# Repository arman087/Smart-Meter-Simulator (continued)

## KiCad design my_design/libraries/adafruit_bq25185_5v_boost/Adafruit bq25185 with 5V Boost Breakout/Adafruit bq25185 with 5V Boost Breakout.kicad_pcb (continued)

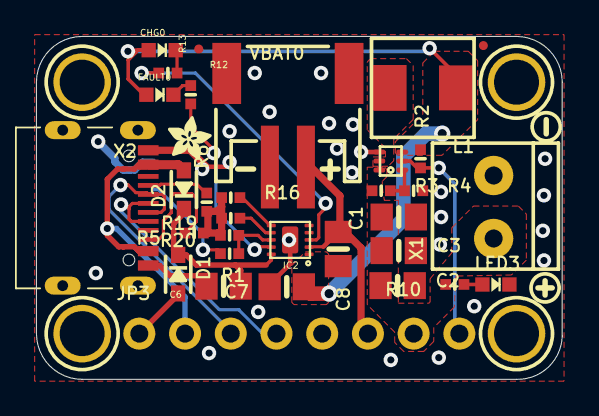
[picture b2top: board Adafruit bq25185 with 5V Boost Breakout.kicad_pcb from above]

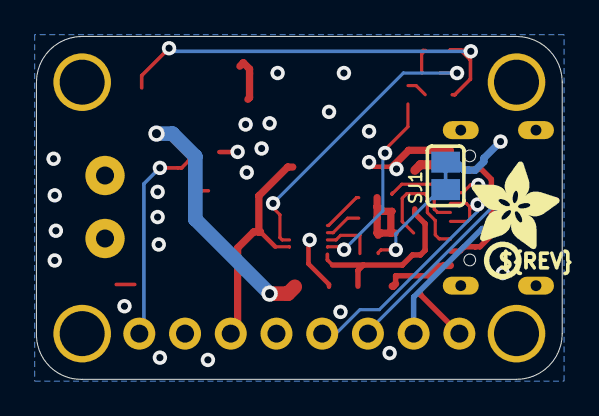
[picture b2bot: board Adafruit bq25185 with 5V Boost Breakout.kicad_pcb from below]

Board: 2 copper layers, 29.2 x 19.0 mm, 66 parts (16 on the bottom side), 23 nets.

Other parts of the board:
PLABEL0: PLABEL0
PLABEL1: PLABEL1
PLABEL2: PLABEL2
PLABEL3: PLABEL3
PLABEL4: PLABEL4
PLABEL5: PLABEL5
PLABEL6: PLABEL6
PLABEL7: PLABEL7
PLABEL8: PLABEL8
PLABEL9: PLABEL9
PLABEL10: PLABEL10
PLABEL12: PLABEL12
PLABEL13: PLABEL13
PLABEL16: PLABEL16
PLABEL17: PLABEL17
PLABEL18: PLABEL18
PLABEL19: PLABEL19
PLABEL20: PLABEL20
PLABEL21: PLABEL21
PLABEL22: PLABEL22
PLABEL23: PLABEL23
PLABEL24: PLABEL24
PLABEL25: PLABEL25
PLABEL26: PLABEL26
U$2: PCBFEAT-REV-040
U$3: SYMBOL_PLUS
U$4: SYMBOL_MINUS
U$26: ADAFRUIT_5MM
U$34: ADAFRUIT_2.5MM
